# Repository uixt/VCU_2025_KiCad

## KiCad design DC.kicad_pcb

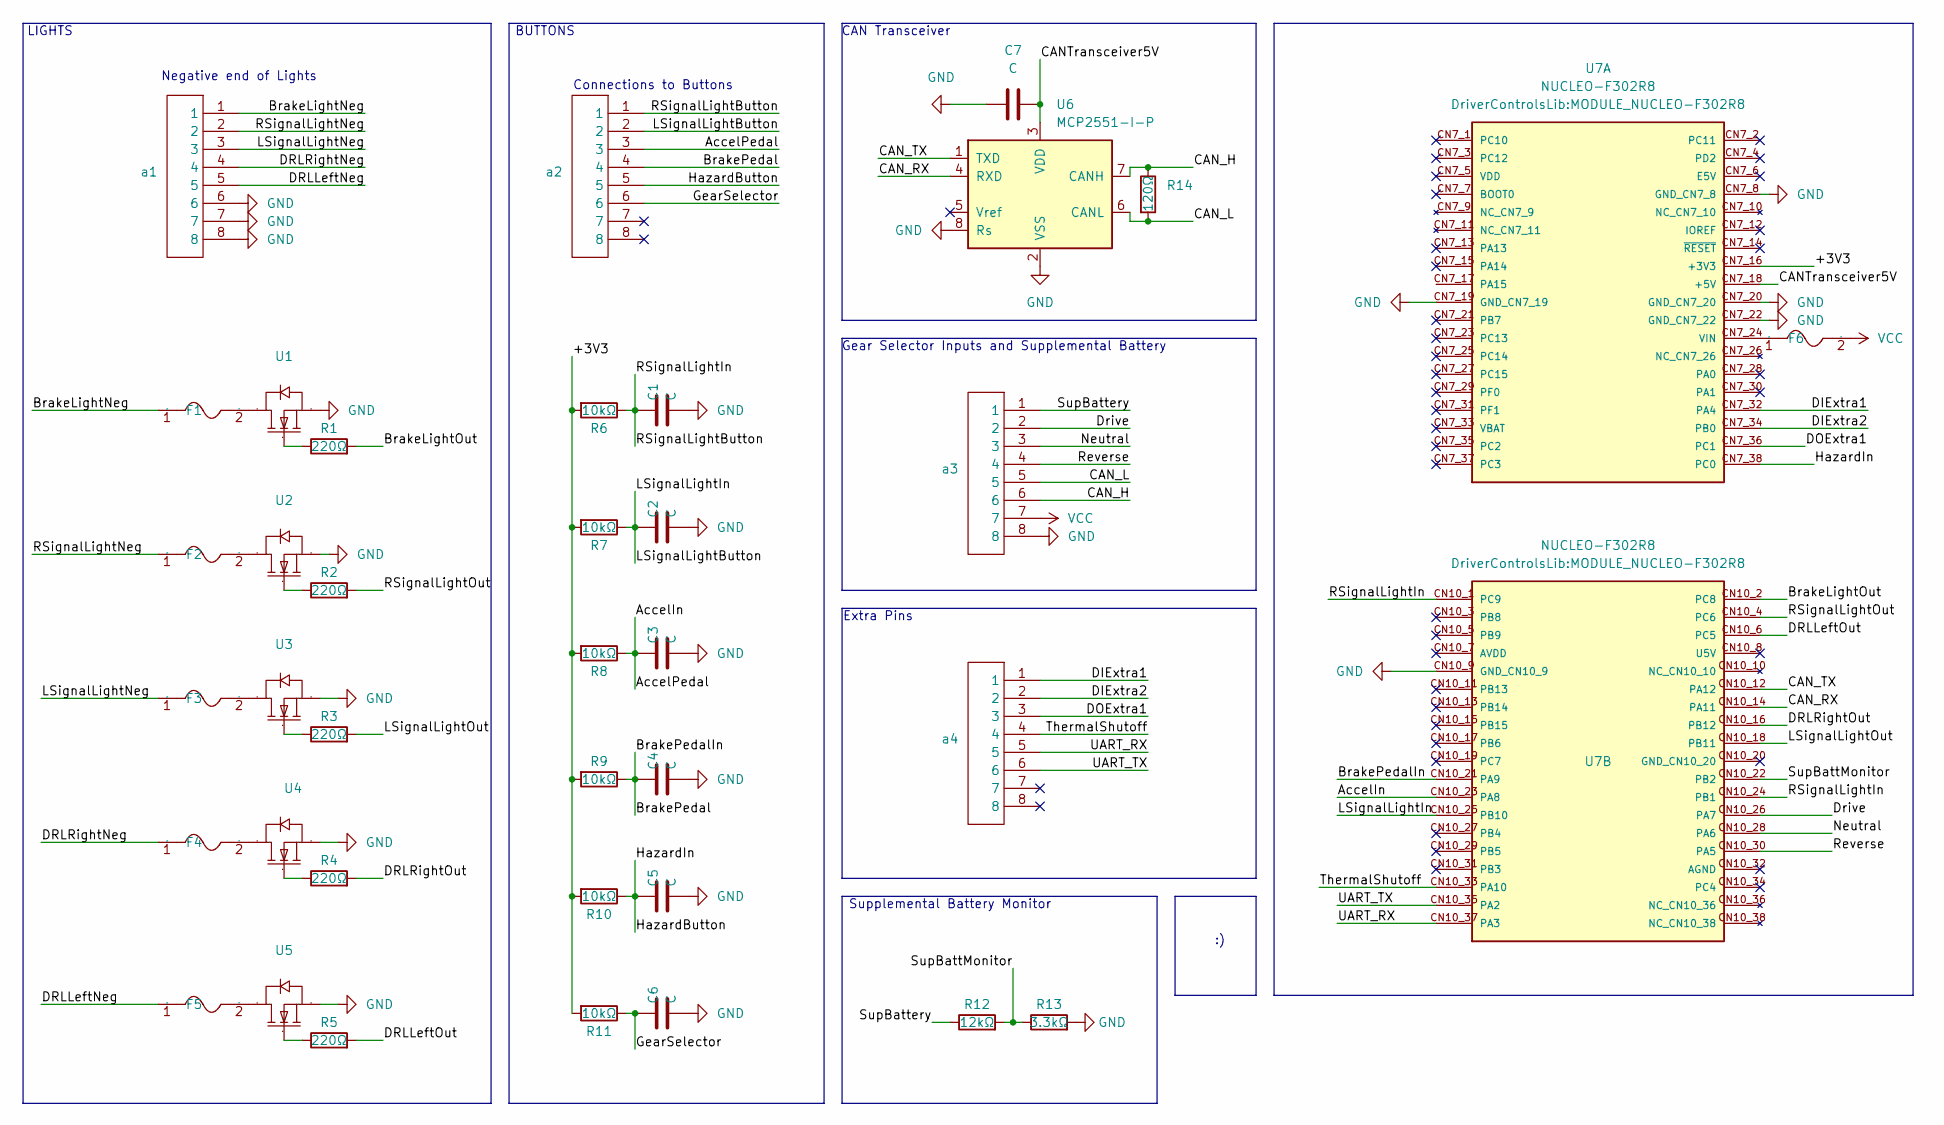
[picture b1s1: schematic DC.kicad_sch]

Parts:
C1, C2, C3, C4, C5, C6, C7: C; CAP-TH_L6.0-W3.5-P7.50-D1.0
F1, F2, F3, F4, F5, F6: FUSE-TH_BD5.4-W22.5-P27.5-D0.8; Manufacturer Part 0001.2511.TR; LCSC Part Name 250V
R1, R2, R3, R4, R5: 220Ω; RES-TH_BD2.2-L6.5-P10.50-D0.6
R6, R7, R8, R9, R10, R11: 10kΩ; RES-TH_BD2.2-L6.5-P10.50-D0.6
R12: 12kΩ; RES-TH_BD2.2-L6.5-P10.50-D0.6
R13: 3.3kΩ; RES-TH_BD2.2-L6.5-P10.50-D0.6
R14: 120Ω; RES-TH_BD2.2-L6.5-P10.50-D0.6
U1, U2, U3, U4, U5: TO220-3_ONS; Manufacturer Part FQP30N06L; LCSC Part Name 1个N沟道 耐压:60V 电流:32A 停产
U6: MCP2551-I-P; DIP-8_W7.62mm
U7: NUCLEO-F302R8; MODULE_NUCLEO-F302R8; PARTREV 17
a1, a2, a3, a4: Molex 8 Pin Mini-fit TPA

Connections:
/+3V3: R6.2, R7.2, R8.2, R9.2, R10.2, R11.2, U7.CN7_16 (+3V3)
/AccelIn: C3.2, R8.1, U7.CN10_23 (PA8), a2.3
/BrakeLightNeg: F1.1, a1.1
/BrakeLightOut: R1.2, U7.CN10_2 (PC8)
/BrakePedal: C4.2, R9.1, U7.CN10_21 (PA9), a2.4
/CANTransceiver5V: C7.2, U6.3 (VDD), U7.CN7_18 (+5V)
/CAN_H: R14.1, U6.7 (CANH), a3.6
/CAN_L: R14.2, U6.6 (CANL), a3.5
/CAN_RX: U6.4 (RXD), U7.CN10_14 (PA11)
/CAN_TX: U6.1 (TXD), U7.CN10_12 (PA12)
/DIExtra1: U7.CN7_32 (PA4), a4.1
/DIExtra2: U7.CN7_34 (PB0), a4.2
/DOExtra1: U7.CN7_36 (PC1), a4.3
/DRLLeftNeg: F5.1, a1.5
/DRLLeftOut: R5.2, U7.CN10_6 (PC5)
/DRLRightNeg: F4.1, a1.4
/DRLRightOut: R4.2, U7.CN10_16 (PB12)
/Drive: U7.CN10_26 (PA7), a3.2
/GearSelector: C6.2, R11.1, a2.6
/HazardButton: C5.2, R10.1, U7.CN7_38 (PC0), a2.5
/LSignalLightButton: C2.2, R7.1, U7.CN10_25 (PB10), a2.2
/LSignalLightNeg: F3.1, a1.3
/LSignalLightOut: R3.2, U7.CN10_18 (PB11)
/Neutral: U7.CN10_28 (PA6), a3.3
/RSignalLightButton: C1.2, R6.1, U7.CN10_1 (PC9), U7.CN10_24 (PB1), a2.1
/RSignalLightNeg: F2.1, a1.2
/RSignalLightOut: R2.2, U7.CN10_4 (PC6)
/Reverse: U7.CN10_30 (PA5), a3.4
/SupBattMonitor: R12.2, R13.1, U7.CN10_22 (PB2)
/SupBattery: R12.1, a3.1
/ThermalShutoff: U7.CN10_33 (PA10), a4.4
/UART_RX: U7.CN10_37 (PA3), a4.5
/UART_TX: U7.CN10_35 (PA2), a4.6
GND: C1.1, C2.1, C3.1, C4.1, C5.1, C6.1, C7.1, R13.2, U1.3 (S), U2.3 (S), U3.3 (S), U4.3 (S), U5.3 (S), U6.2 (VSS), U6.8 (Rs), U7.CN7_8 (GND_CN7_8), U7.CN7_19 (GND_CN7_19), U7.CN7_20 (GND_CN7_20), U7.CN7_22 (GND_CN7_22), U7.CN10_9 (GND_CN10_9), a1.6, a1.7, a1.8, a3.8
unnamed: F1.2, U1.2 (D)
unnamed: R1.1, U1.1 (G)
unnamed: F2.2, U2.2 (D)
unnamed: R2.1, U2.1 (G)
unnamed: F3.2, U3.2 (D)
unnamed: R3.1, U3.1 (G)
unnamed: F4.2, U4.2 (D)
unnamed: R4.1, U4.1 (G)
unnamed: F5.2, U5.2 (D)
unnamed: R5.1, U5.1 (G)
unnamed: F6.1, U7.CN7_24 (VIN)
VCC: F6.2, a3.7

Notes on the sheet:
Extra Pins
Negative end of Lights
Supplemental Battery Monitor
CAN Transceiver
BUTTONS
Gear Selector Inputs and Supplemental Battery
Connections to Buttons
LIGHTS

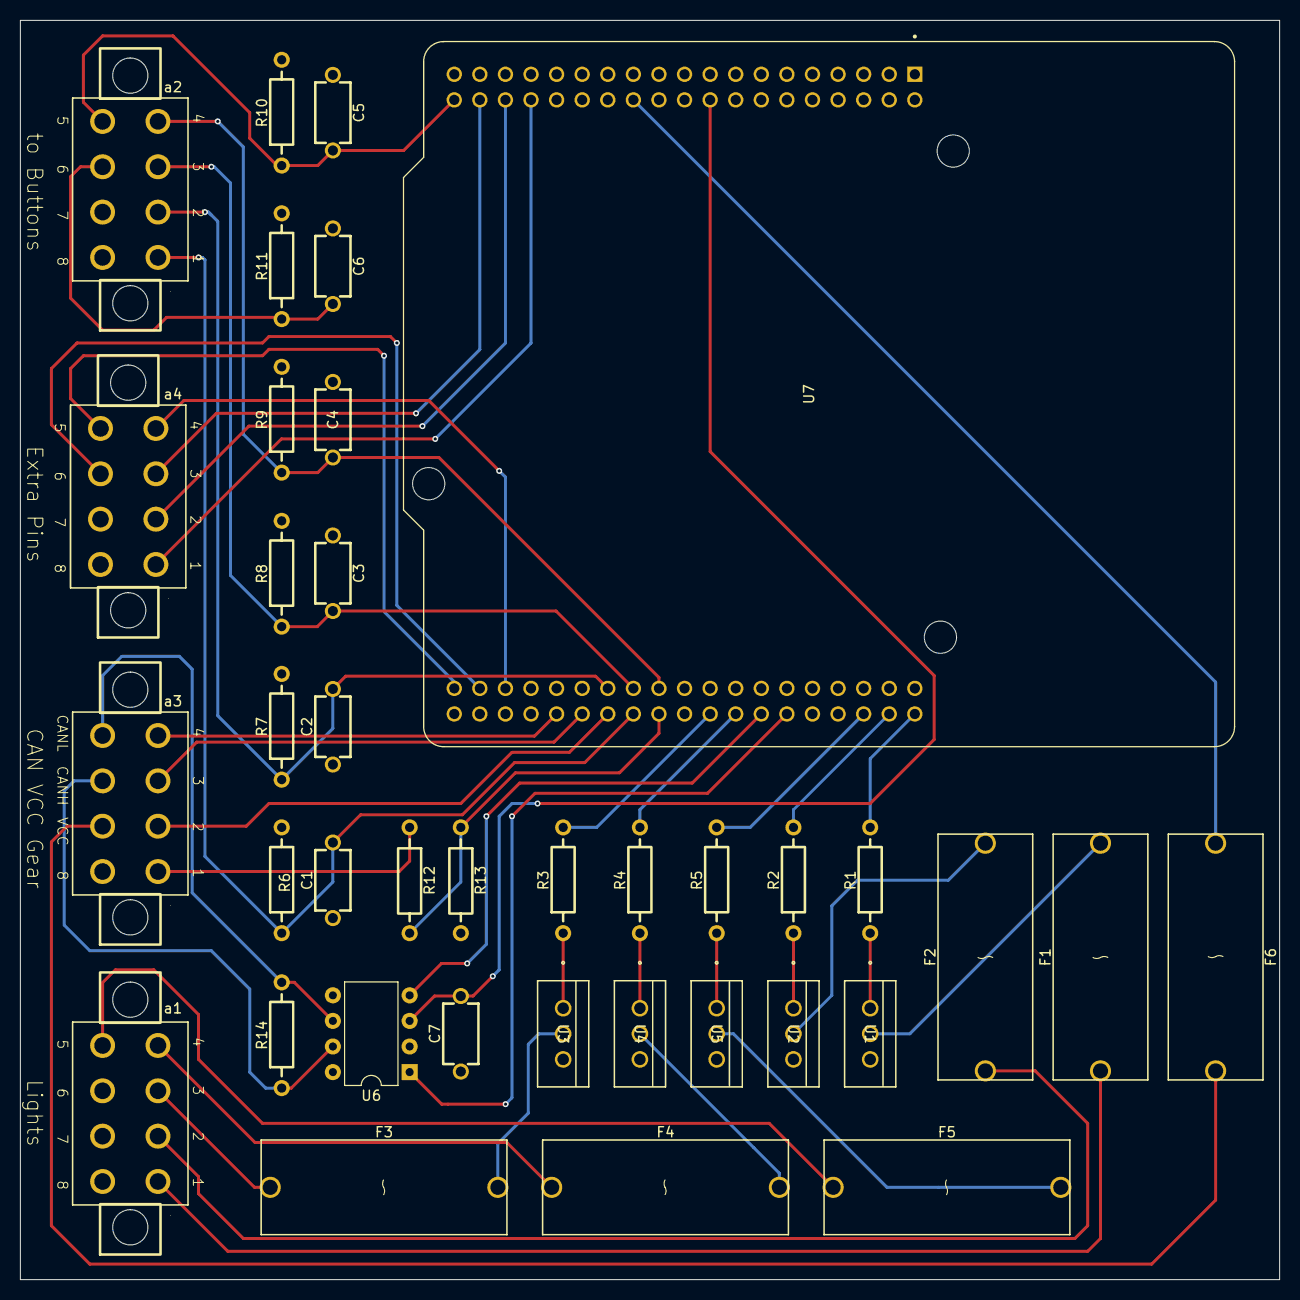
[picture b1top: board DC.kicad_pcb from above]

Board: 4 copper layers, 125.0 x 125.0 mm, 38 parts (0 on the bottom side), 46 nets.

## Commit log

2024-12-25 shared the wrong files'
2024-12-25 updated files
2024-12-26 added inrush current resistors and fixed gear switch circuit
2024-12-27 changed mosfet circuit
2024-12-27 fixed the lights mosfets, removed inrush resistors
2024-12-27 almost final draft
2024-12-30 pcb tolerances setup, component arrangement
2025-01-07 pcb routing, reassignment of stm32 pins
2025-01-07 finished first draft of routing
2025-01-09 fixed labels
